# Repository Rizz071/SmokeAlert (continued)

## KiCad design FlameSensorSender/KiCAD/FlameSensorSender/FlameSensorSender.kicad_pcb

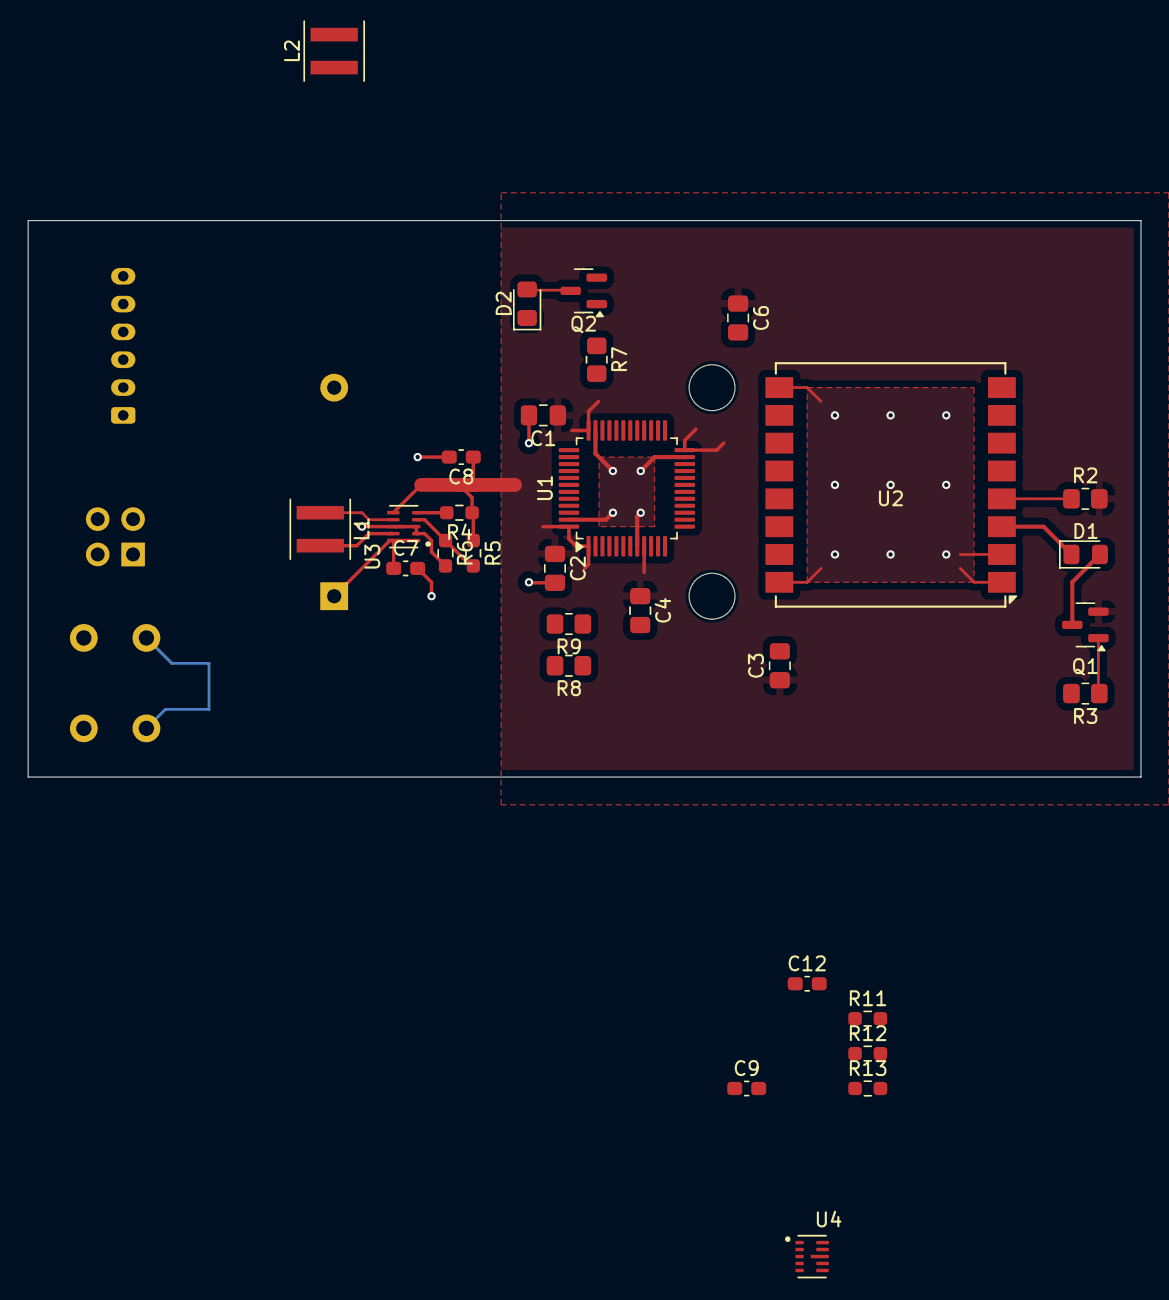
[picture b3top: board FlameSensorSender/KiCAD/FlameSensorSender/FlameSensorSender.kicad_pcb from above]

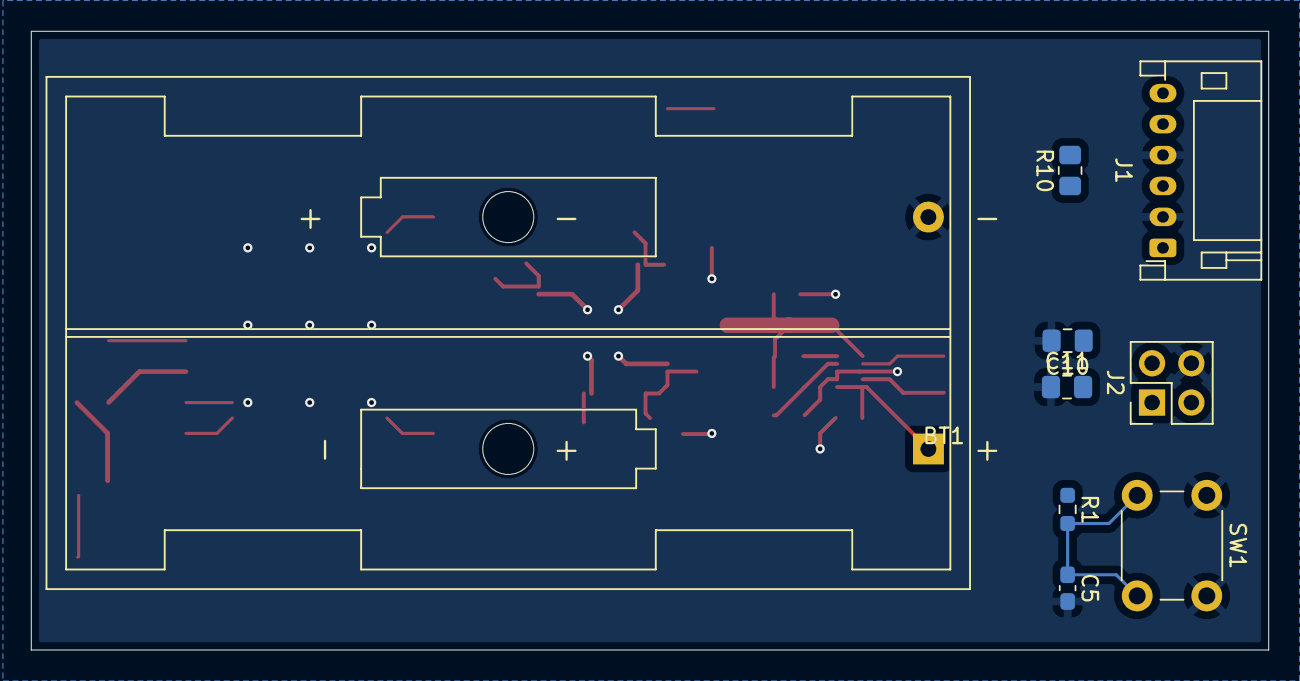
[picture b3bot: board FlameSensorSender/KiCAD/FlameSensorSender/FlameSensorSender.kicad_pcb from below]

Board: 2 copper layers, 80.0 x 40.0 mm, 39 parts (9 on the bottom side), 33 nets.

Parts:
BT1: AA 2pcs 3V0-3V6 at start; BatteryHolder_Keystone_2462_2xAA
C1, C2, C3, C4, C6: 100n; C_0805_2012Metric_Pad1.18x1.45mm_HandSolder
C5: 105, 0603; C_0603_1608Metric_Pad1.08x0.95mm_HandSolder
C7, C8, C9, C12: 22u; C_0603_1608Metric_Pad1.08x0.95mm_HandSolder
C10: 220n; C_0805_2012Metric_Pad1.18x1.45mm_HandSolder
C11: 104, 0805; C_0805_2012Metric_Pad1.18x1.45mm_HandSolder
D1, D2: 1N5819; D_0805_2012Metric_Pad1.15x1.40mm_HandSolder
J1: Sharp GP2Y1014AUOF; JST_PH_S6B-PH-K_1x06_P2.00mm_Horizontal
J2: SWD; PinHeader_2x02_P2.54mm_Vertical
L1, L2: 470n; L_Coilcraft_XxL4020
Q1, Q2: AO3400A; SOT-23
R1: 10k, 0603; R_0603_1608Metric_Pad0.98x0.95mm_HandSolder
R2, R3, R7: 10k; R_0805_2012Metric_Pad1.20x1.40mm_HandSolder
R4, R11: 100k Rpg; R_0603_1608Metric_Pad0.98x0.95mm_HandSolder
R5: 511k Rfbt; R_0603_1608Metric_Pad0.98x0.95mm_HandSolder
R6, R13: 91k Rfbb; R_0603_1608Metric_Pad0.98x0.95mm_HandSolder
R8: 220; R_0805_2012Metric_Pad1.20x1.40mm_HandSolder
R9: 330; R_0805_2012Metric_Pad1.20x1.40mm_HandSolder
R10: 150; R_0805_2012Metric_Pad1.20x1.40mm_HandSolder
R12: 806k Rfbt; R_0603_1608Metric_Pad0.98x0.95mm_HandSolder
SW1: SW_Push; SW_PUSH_6mm_H4.3mm
U1: STM32F103C6Tx; LQFP-48_7x7mm_P0.5mm
U2: Ai-Thinker-Ra-02; Ai-Thinker-Ra-01-LoRa
U3, U4: TPS63802DLAR; VREG_TPS63802DLAR

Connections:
/+3V3 regulated: C1.1, C2.1, C3.1, C4.1, C6.1, C8.1, C11.2, J2.1, Q1.2 (S), R1.1, R2.2, R4.1, R5.1, U1.1 (VBAT), U1.9 (VDDA), U1.24 (VDD), U1.36 (VDD), U1.48 (VDD), U3.6 (VOUT)
/+5V0 regulated: C12.1, Q2.2 (S), R11.1, R12.1, U4.6 (VOUT)
/BATTERY_IN: BT1.1 (+), C7.1, C9.1, U3.1 (EN), U3.10 (VIN), U4.1 (EN), U4.10 (VIN)
/LORA EN: R3.2, U1.22 (PB11)
/PB0: U1.18 (PB0), U2.5 (DIO0)
/PB12: J1.3, U1.25 (PB12)
/RESET_PIN: C5.1, R1.2, SW1.2, U1.7 (NRST)
/SENSOR DATA: R8.1, R9.1, U1.10 (PA0)
/SENSOR EN: R7.2, U1.21 (PB10)
/SWCLK: J2.3, U1.37 (PA14)
/SWDIO: J2.2, U1.34 (PA13)
GNDD: BT1.2 (-), C1.2, C2.2, C3.2, C4.2, C5.2, C6.2, C7.2, C8.2, C9.2, C10.2, C11.1, C12.2, J1.2, J1.4, J2.4, R6.2, R9.2, R13.2, SW1.1, U1.8 (VSSA), U1.23 (VSS), U1.35 (VSS), U1.47 (VSS), U2.1 (GND), U2.2 (GND), U2.9 (GND), U2.16 (GND), U3.2 (MODE), U3.3 (AGND), U3.8 (GND), U4.2 (MODE), U4.3 (AGND), U4.8 (GND)
unnamed: D1.2 (A), Q1.3 (D)
unnamed: D1.1 (K), U2.3 (VDD)
unnamed: D2.2 (A), Q2.3 (D)
unnamed: D2.1 (K), J1.6, R10.2
unnamed: C10.1, J1.1, R10.1
unnamed: J1.5, R8.2
unnamed: Q1.1 (G), R3.1
unnamed: Q2.1 (G), R7.1
unnamed: U1.14 (PA4), U2.15 (~NSS)
unnamed: U1.15 (PA5), U2.12 (SCK)
unnamed: U1.16 (PA6), U2.13 (MISO)
unnamed: U1.17 (PA7), U2.14 (MOSI)
unnamed: R2.1, U2.4 (~RESET)
unnamed: R5.2, R6.1, U3.4 (FB)
unnamed: L1.2, U3.9 (L1)
unnamed: L1.1, U3.7 (L2)
unnamed: R4.2, U3.5 (PG)
unnamed: R12.2, R13.1, U4.4 (FB)
unnamed: L2.2, U4.9 (L1)
unnamed: L2.1, U4.7 (L2)
unnamed: R11.2, U4.5 (PG)

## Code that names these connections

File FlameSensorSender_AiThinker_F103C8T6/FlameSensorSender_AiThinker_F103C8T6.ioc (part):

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Mcu.Name=STM32F103C(8-B)Tx
Mcu.Package=LQFP48
Mcu.UserName=STM32F103C8Tx
PA0-WKUP.GPIOParameters=GPIO_Label
PA0-WKUP.GPIO_Label=V0
PA0-WKUP.Signal=ADCx_IN0
PA1.GPIOParameters=GPIO_Label
PA1.GPIO_Label=VCC_BAT
PA1.Signal=ADCx_IN1
PA10.Mode=Asynchronous
PA10.Signal=USART1_RX
PA13.Mode=Serial_Wire
PA13.Signal=SYS_JTMS-SWDIO
PA14.Mode=Serial_Wire
PA14.Signal=SYS_JTCK-SWCLK
PA15.GPIOParameters=GPIO_Label
PA15.GPIO_Label=BUZZER
PA15.Signal=GPIO_Output
PA4.GPIOParameters=GPIO_Speed,PinState,GPIO_PuPd,GPIO_Label
PA4.GPIO_Label=LORA_NSS
PA4.GPIO_PuPd=GPIO_PULLUP
PA4.GPIO_Speed=GPIO_SPEED_FREQ_HIGH
PA4.PinState=GPIO_PIN_SET
PA4.Signal=GPIO_Output
PA5.Mode=Full_Duplex_Master
PA5.Signal=SPI1_SCK
PA6.Mode=Full_Duplex_Master
PA6.Signal=SPI1_MISO
PA7.Mode=Full_Duplex_Master
PA7.Signal=SPI1_MOSI
PA9.Mode=Asynchronous
PA9.Signal=USART1_TX
PB0.GPIOParameters=GPIO_PuPd,GPIO_Label
PB0.GPIO_Label=LORA_DIO1
PB0.GPIO_PuPd=GPIO_PULLDOWN
PB0.Signal=GPXTI0
PB1.GPIOParameters=PinState,GPIO_PuPd,GPIO_Label
PB1.GPIO_Label=LORA_NRST
PB1.GPIO_PuPd=GPIO_PULLUP
PB1.PinState=GPIO_PIN_SET
PB1.Signal=GPIO_Output
PB10.GPIOParameters=GPIO_PuPd,GPIO_Label
PB10.GPIO_Label=MOSFET_GATE_SENSOR
PB10.GPIO_PuPd=GPIO_PULLDOWN
PB10.Signal=GPIO_Output
PB11.GPIOParameters=PinState,GPIO_PuPd,GPIO_Label
PB11.GPIO_Label=MOSFET_GATE_LORA
PB11.GPIO_PuPd=GPIO_PULLDOWN
PB11.PinState=GPIO_PIN_RESET
PB11.Signal=GPIO_Output
PB12.GPIOParameters=GPIO_Speed,PinState,GPIO_PuPd,GPIO_Label
PB12.GPIO_Label=V-LED
PB12.GPIO_PuPd=GPIO_NOPULL
PB12.GPIO_Speed=GPIO_SPEED_FREQ_HIGH
PB12.PinState=GPIO_PIN_SET
PB12.Signal=GPIO_Output
PB2.GPIOParameters=GPIO_Label
PB2.GPIO_Label=LORA_BUSY
PB2.Signal=GPIO_Input
PC13-TAMPER-RTC.GPIOParameters=PinState,GPIO_Label
PC13-TAMPER-RTC.GPIO_Label=SMALL_INFO_LED
PC13-TAMPER-RTC.PinState=GPIO_PIN_SET
PC13-TAMPER-RTC.Signal=GPIO_Output
PC14-OSC32_IN.GPIOParameters=PinState,GPIO_PuPd,GPIO_Label,GPIO_ModeDefaultOutputPP
PC14-OSC32_IN.GPIO_Label=INFO_LED
PC14-OSC32_IN.GPIO_ModeDefaultOutputPP=GPIO_MODE_OUTPUT_PP
PC14-OSC32_IN.GPIO_PuPd=GPIO_NOPULL
PC14-OSC32_IN.PinState=GPIO_PIN_RESET
PC14-OSC32_IN.Signal=GPIO_Output
RCC.SYSCLKFreq_VALUE=8000000
RCC.SYSCLKSource=RCC_SYSCLKSOURCE_PLLCLK
board=custom

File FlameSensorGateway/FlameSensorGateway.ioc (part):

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Mcu.Name=STM32H562RGTx
Mcu.Package=LQFP64
Mcu.UserName=STM32H562RGTx
PA1.GPIOParameters=GPIO_PuPd,GPIO_Label
PA1.GPIO_Label=LORA_DIO1
PA1.GPIO_PuPd=GPIO_PULLDOWN
PA1.Signal=GPXTI1
PA10.Mode=Asynchronous
PA10.Signal=LPUART1_RX
PA13(JTMS/SWDIO).Mode=Serial_Wire
PA13(JTMS/SWDIO).Signal=DEBUG_JTMS-SWDIO
PA14(JTCK/SWCLK).Mode=Serial_Wire
PA14(JTCK/SWCLK).Signal=DEBUG_JTCK-SWCLK
PA2.GPIOParameters=GPIO_PuPd,GPIO_Label
PA2.GPIO_Label=LORA_BUSY
PA2.GPIO_PuPd=GPIO_NOPULL
PA2.Signal=GPIO_Input
PA3.GPIOParameters=GPIO_Speed,PinState,GPIO_PuPd,GPIO_Label
PA3.GPIO_Label=LORA_NRST
PA3.GPIO_PuPd=GPIO_PULLUP
PA3.GPIO_Speed=GPIO_SPEED_FREQ_VERY_HIGH
PA3.PinState=GPIO_PIN_SET
PA3.Signal=GPIO_Output
PA4.GPIOParameters=PinState,GPIO_PuPd,GPIO_Label
PA4.GPIO_Label=LORA_NSS
PA4.GPIO_PuPd=GPIO_PULLUP
PA4.PinState=GPIO_PIN_SET
PA4.Signal=GPIO_Output
PA5.Mode=Full_Duplex_Master
PA5.Signal=SPI1_SCK
PA6.Mode=Full_Duplex_Master
PA6.Signal=SPI1_MISO
PA7.Mode=Full_Duplex_Master
PA7.Signal=SPI1_MOSI
PA9.Mode=Asynchronous
PA9.Signal=LPUART1_TX
PB14.Mode=Asynchronous
PB14.Signal=USART1_TX
PB15.Mode=Asynchronous
PB15.Signal=USART1_RX
PB2.GPIOParameters=PinState,GPIO_PuPd,GPIO_Label
PB2.GPIO_Label=SMALL_INFO_LED
PB2.GPIO_PuPd=GPIO_PULLDOWN
PB2.PinState=GPIO_PIN_RESET
PB2.Signal=GPIO_Output
PB6.Mode=I2C
PB6.Signal=I2C1_SCL
PB7.Mode=I2C
PB7.Signal=I2C1_SDA
PC14-OSC32_IN(OSC32_IN).Mode=LSE-External-Oscillator
PC14-OSC32_IN(OSC32_IN).Signal=RCC_OSC32_IN
PC15-OSC32_OUT(OSC32_OUT).Mode=LSE-External-Oscillator
PC15-OSC32_OUT(OSC32_OUT).Signal=RCC_OSC32_OUT
PH0-OSC_IN(PH0).Mode=HSE-External-Oscillator
PH0-OSC_IN(PH0).Signal=RCC_OSC_IN
PH1-OSC_OUT(PH1).Mode=HSE-External-Oscillator
PH1-OSC_OUT(PH1).Signal=RCC_OSC_OUT
RCC.HSE_VALUE=25000000
RCC.SYSCLKFreq_VALUE=250000000
RCC.SYSCLKSource=RCC_SYSCLKSOURCE_PLLCLK
board=custom

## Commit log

2025-05-04 added Shared folder
2025-07-24 lora setup done 70%
2025-09-09 CRUD tests done
